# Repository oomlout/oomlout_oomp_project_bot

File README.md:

# oomlout_oomp_documentation_bot_v2

## actions

* action_setup.py -- sets up data and structure
* action_generate_kicad_from_eagle.py -- take all .brd eagle files, open in kicad and save as kicad_pcb and a kicad_sch file
* action_generate_kicad_outputs.py -- (not used anymore) generate the outputs using robo mouse, takes in a kicad_pcb and kicad_sch file
* action_generate_kibot_outputs.py -- all directories with kicad_pcb files get the kibot template from templates/kibot_template.yaml copied to them and kibot is run if the report.txt doesn't exist
* action_generate_image_resolutions.py -- generate resolutions of images
* action_generate_readmes -- generate all the readmes
* action_cleanup_project.py -- cleans up unwanted files from a project directory
* action_harvest_parts.py -- take the working_bom.csv and add parts_verbose to yaml file
* action_match_parts.py -- go trhough each part and match parts_verbose aprts with parts_oomp
* action_find_part.py -- go through all projects and compile a list of all the entries with  search term
* action_rescue_old_kicad_schematic.py -- go through and find all directories that have a kicad_pcb and a .sch file and no schematics generated. Open in kicad 5 and save.

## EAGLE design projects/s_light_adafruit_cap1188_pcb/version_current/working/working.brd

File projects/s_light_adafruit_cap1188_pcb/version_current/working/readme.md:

# Adafruit-CAP1188-PCB by s-light  
This is a harvested standardized copy of a project from github.  
The original project can be found at:  
https://github.com/s-light/Adafruit-CAP1188-PCB  
Please consult that link for additional, details, files, and license information.  
Note: It was auto harvested and if the original repo had more than one board file or anything out of the ordinary the files here are likely not representative.

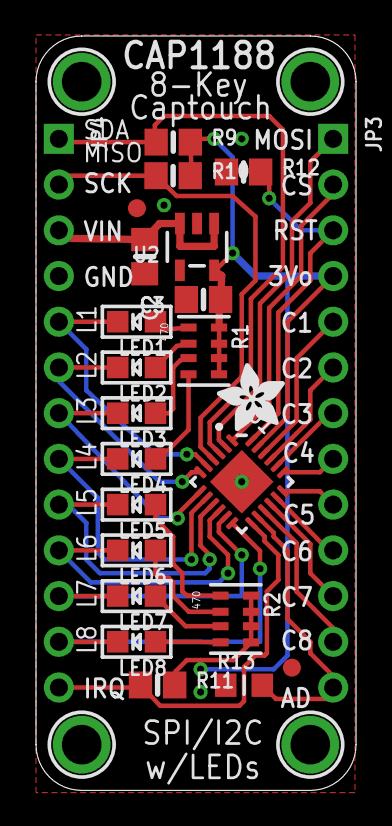
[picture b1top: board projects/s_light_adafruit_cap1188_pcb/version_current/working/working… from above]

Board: 2 copper layers, 17.8 x 41.9 mm, 29 parts (1 on the bottom side), 34 nets.

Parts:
C2, C3: 10uF; 0805-NO
FID1, FID2: FIDUCIAL""; FIDUCIAL_1MM
JP3, JP4: 1X13_ROUND_70
LED1, LED2, LED3, LED4, LED5, LED6, LED7, LED8: CHIPLED_0805
R1, R2: 470; RESPACK_4X0603
R9, R10, R11, R12: 10K; 0805-NO
R13: 150K; _0805MP
U1: QFN24_4MM_SMSC
U2: MIC5225-3; SOT23-5
U$7, U$8, U$9, U$10: MOUNTINGHOLE2.0; MOUNTINGHOLE_2.0_PLATED
U$13: ADAFRUIT_3.5MM
U$14: ADAFRUIT_9MM

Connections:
3.3V: C3.1, JP3.4, R1.5, R1.6, R1.7, R1.8, R2.5, R2.6, R2.7, R2.8, R9.2, R10.2, R11.2, U1.23, U2.5
ADDR: JP3.13, R13.2, U1.14
CS: JP3.2, U1.1
CS1: JP3.5, U1.22
CS2: JP3.6, U1.21
CS3: JP3.7, U1.20
CS4: JP3.8, U1.19
CS5: JP3.9, U1.18
CS6: JP3.10, U1.17
CS7: JP3.11, U1.16
CS8: JP3.12, U1.15
GND: C2.2, C3.2, JP4.4, R12.1, R13.1, U1.THERM, U2.2
IRQ: JP4.13, R11.1, U1.13
LED1: JP4.5, LED1.C, U1.5
LED2: JP4.6, LED2.C, U1.6
LED3: JP4.7, LED3.C, U1.7
LED4: JP4.8, LED4.C, U1.8
LED5: JP4.9, LED5.C, U1.9
LED6: JP4.10, LED6.C, U1.10
LED7: JP4.11, LED7.C, U1.11
LED8: JP4.12, LED8.C, U1.12
unnamed: LED1.A, R1.1
unnamed: LED2.A, R1.2
unnamed: LED3.A, R1.3
unnamed: LED4.A, R1.4
unnamed: LED5.A, R2.1
unnamed: LED6.A, R2.2
unnamed: LED7.A, R2.3
unnamed: LED8.A, R2.4
RESET: JP3.3, R12.2, U1.24
SCK: JP4.2, R10.1, U1.4
SDA/MISO: JP4.1, R9.1, U1.3
VIN: C2.1, JP4.3, U2.1, U2.3
WAKE/MOSI: JP3.1, U1.2

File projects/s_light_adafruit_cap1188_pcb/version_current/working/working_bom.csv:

"Id";"Designator";"Footprint";"Quantity";"Designation";"Supplier and ref";
1;"JP3,JP4";"1X13_ROUND_70";2;"";;;
2;"U2";"SOT23-5";1;"MIC5225-3";;;
3;"LED8,LED2,LED6,LED4,LED7,LED5,LED3,LED1";"CHIPLED_0805";8;"";;;
4;"R9,R12,R11,R10";"0805-NO";4;"10K";;;
5;"U1";"QFN24_4MM_SMSC";1;"";;;
6;"R2,R1";"RESPACK_4X0603";2;"470";;;
7;"U$9,U$7,U$8,U$10";"MOUNTINGHOLE_2.0_PLATED";4;"MOUNTINGHOLE2.0";;;
8;"U$13";"ADAFRUIT_3.5MM";1;"";;;
9;"FID2,FID1";"FIDUCIAL_1MM";2;"FIDUCIAL""";;;
10;"C2,C3";"0805-NO";2;"10uF";;;
11;"R13";"_0805MP";1;"150K";;;
12;"U$14";"ADAFRUIT_9MM";1;"";;;

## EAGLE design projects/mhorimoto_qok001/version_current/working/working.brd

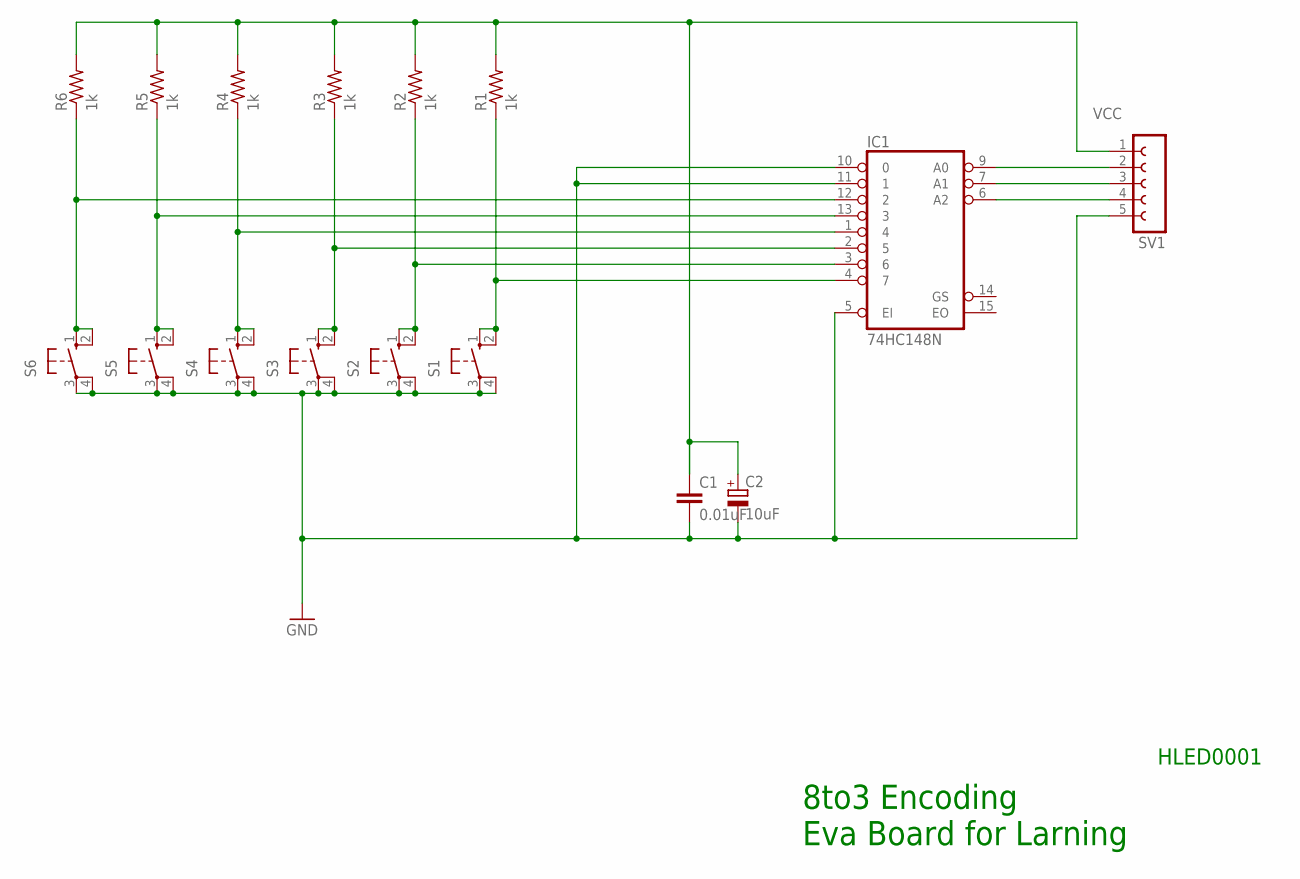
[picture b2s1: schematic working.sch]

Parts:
C1: 0.01uF; C025-025X050
C2: 10uF; E2,5-6E
IC1: 74HC148N; DIL16
R1, R2, R3, R4, R5, R6: 1k; 0207/7
S1, S2, S3, S4, S5, S6: 10-XX; B3F-10XX
SV1: FE05-1

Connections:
GND: C1.2, C2.-, IC1.5 (EI), IC1.8 (GND), IC1.10 (0), IC1.11 (1), S1.3, S1.4 (P1), S2.3, S2.4 (P1), S3.3, S3.4 (P1), S4.3, S4.4 (P1), S5.3, S5.4 (P1), S6.3, S6.4 (P1), SV1.5
unnamed: IC1.4 (7), R1.1, S1.1 (S), S1.2 (S1)
unnamed: IC1.3 (6), R2.1, S2.1 (S), S2.2 (S1)
unnamed: IC1.2 (5), R3.1, S3.1 (S), S3.2 (S1)
unnamed: IC1.1 (4), R4.1, S4.1 (S), S4.2 (S1)
unnamed: IC1.13 (3), R5.1, S5.1 (S), S5.2 (S1)
unnamed: IC1.12 (2), R6.1, S6.1 (S), S6.2 (S1)
unnamed: IC1.9 (A0), SV1.2
unnamed: IC1.7 (A1), SV1.3
unnamed: IC1.6 (A2), SV1.4
VCC: C1.1, C2.+, IC1.16 (VCC), R1.2, R2.2, R3.2, R4.2, R5.2, R6.2, SV1.1

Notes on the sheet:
HLED0001
8to3 Encoding Eva Board for Larning

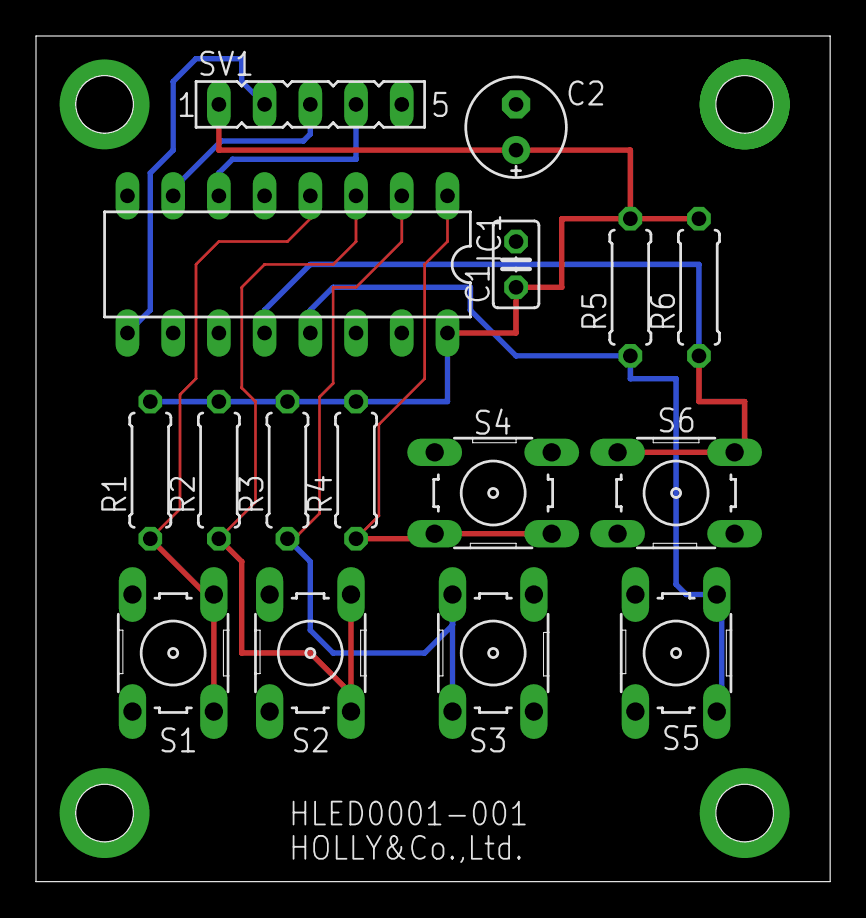
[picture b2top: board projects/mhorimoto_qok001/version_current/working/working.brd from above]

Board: 2 copper layers, 44.1 x 47.0 mm, 16 parts (0 on the bottom side), 11 nets.

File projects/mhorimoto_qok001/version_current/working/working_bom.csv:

"Id";"Designator";"Footprint";"Quantity";"Designation";"Supplier and ref";
1;"S3,S5,S2,S6,S1,S4";"B3F-10XX";6;"";;;
2;"R2,R6,R4,R5,R3,R1";"0207_7";6;"1k";;;
3;"@HOLE0,@HOLE1,@HOLE3,@HOLE2";"";4;"";;;
4;"C1";"C025-025X050";1;"0.01uF";;;
5;"SV1";"FE05-1";1;"";;;
6;"C2";"E2,5-6E";1;"10uF";;;
7;"IC1";"DIL16";1;"74HC148N";;;

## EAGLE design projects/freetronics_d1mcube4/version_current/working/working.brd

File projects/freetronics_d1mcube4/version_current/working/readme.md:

# OOMP Project  
## D1MCUBE4  by freetronics  
  
oomp key: oomp_projects_flat_freetronics_d1mcube4  
(snippet of original readme)  
  
4x4x4 RGB LED Cube for the WeMos D1 Mini  
=========================================  
  
Copyright 2017 Freetronics Pty Ltd  www.freetronics.com.au    
  
4x4x4 RGB LED cube that can be controlled by a [WeMos D1 Mini][1], a  
microcontroller board based on the ESP8266 module.  
  
Features:  
  
 * 64 x 8mm addressable RGB LEDs (APA106)  
 * 2.1mm DC jack and solder terminal connections for power input.  
  
More information is available at:  
  
  http://www.freetronics.com.au/d1mcube4  

INSTALLATION  
------------  
The design is saved as an EAGLE project. EAGLE PCB design software is  
available from www.cadsoftusa.com free for non-commercial use. To use  
this project download it and place the directory containing these files  
into the "eagle" directory on your computer, then navigate to the  
project.  

DISTRIBUTION  
------------  
The specific terms of distribution of this project are governed by the  
license referenced below.  

LICENSE  
-------  
Licensed under the TAPR Open Hardware License (www.tapr.org/OHL).  
The "license" folder within this repository also contains a copy of  
this license in plain text format.  

[1]: http://www.wemos.cc/wiki/doku.php?id=en:d1_mini  

  full source readme at [readme_src.md](readme_src.md)  
  
source repo at: [https://github.com/freetronics/D1MCUBE4](https://github.com/freetronics/D1MCUBE4)  
## Board  

## Schematic  

[schematic pdf](working_schematic.pdf)  
## Images

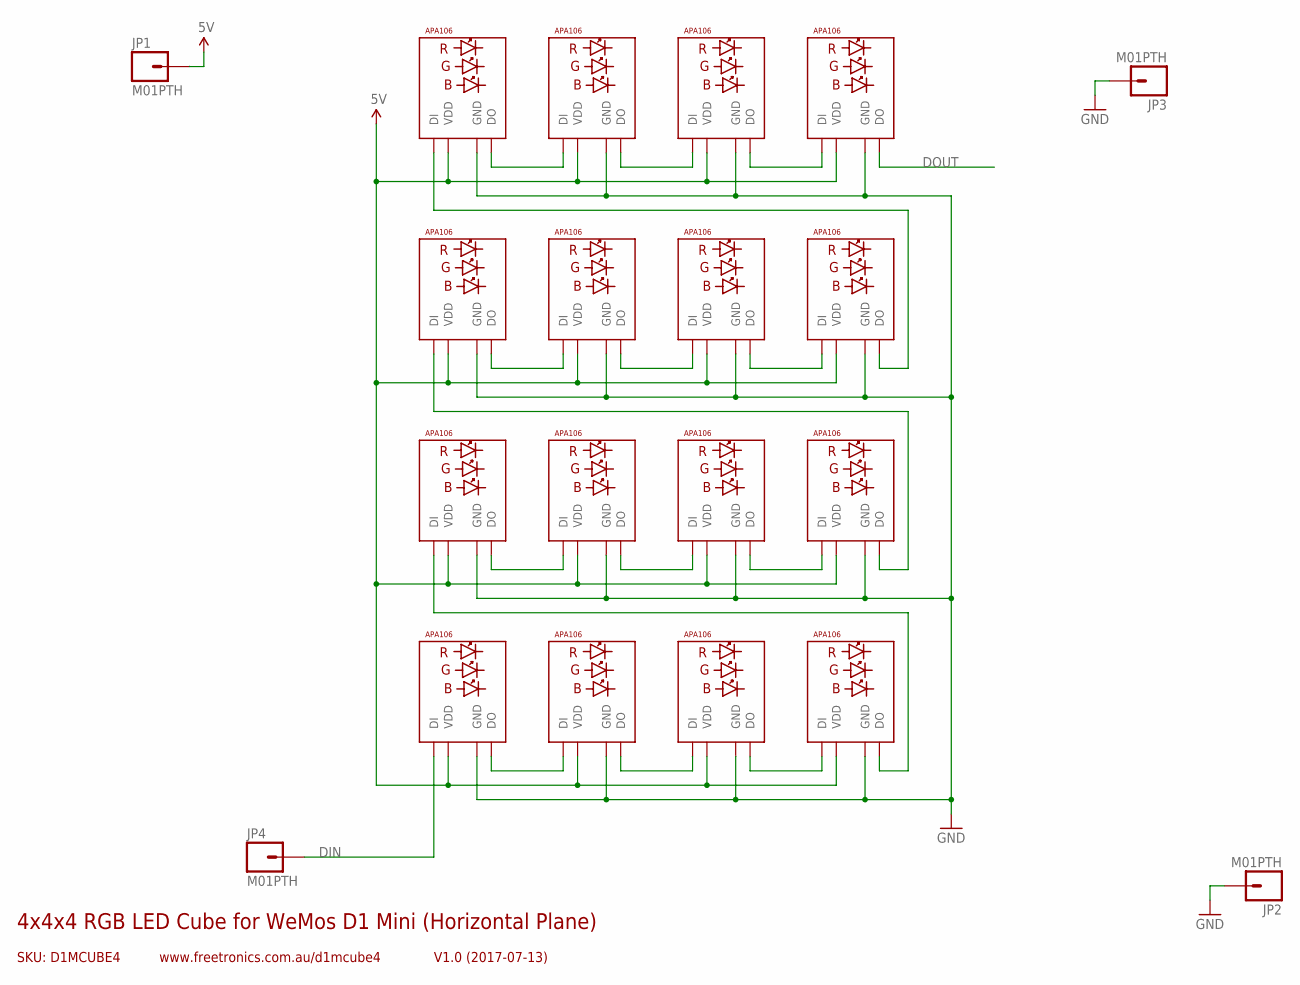
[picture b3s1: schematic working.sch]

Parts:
JP1, JP2, JP3, JP4: M01PTH; 1X01
LED1, LED2, LED3, LED4, LED5, LED6, LED7, LED8, LED9, LED10, LED11, LED12, LED13, LED14, LED15, LED16: APA106F8; LED8MMRGB

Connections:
5V: JP1.1, LED1.3 (VDD), LED2.3 (VDD), LED3.3 (VDD), LED4.3 (VDD), LED5.3 (VDD), LED6.3 (VDD), LED7.3 (VDD), LED8.3 (VDD), LED9.3 (VDD), LED10.3 (VDD), LED11.3 (VDD), LED12.3 (VDD), LED13.3 (VDD), LED14.3 (VDD), LED15.3 (VDD), LED16.3 (VDD)
DIN: JP4.1, LED1.4 (DI)
DOUT: LED16.1 (DO)
GND: JP2.1, JP3.1, LED1.2 (GND), LED2.2 (GND), LED3.2 (GND), LED4.2 (GND), LED5.2 (GND), LED6.2 (GND), LED7.2 (GND), LED8.2 (GND), LED9.2 (GND), LED10.2 (GND), LED11.2 (GND), LED12.2 (GND), LED13.2 (GND), LED14.2 (GND), LED15.2 (GND), LED16.2 (GND)
unnamed: LED1.1 (DO), LED2.4 (DI)
unnamed: LED2.1 (DO), LED3.4 (DI)
unnamed: LED3.1 (DO), LED4.4 (DI)
unnamed: LED13.1 (DO), LED14.4 (DI)
unnamed: LED14.1 (DO), LED15.4 (DI)
unnamed: LED15.1 (DO), LED16.4 (DI)
unnamed: LED9.1 (DO), LED10.4 (DI)
unnamed: LED10.1 (DO), LED11.4 (DI)
unnamed: LED11.1 (DO), LED12.4 (DI)
unnamed: LED5.1 (DO), LED6.4 (DI)
unnamed: LED6.1 (DO), LED7.4 (DI)
unnamed: LED7.1 (DO), LED8.4 (DI)
unnamed: LED12.1 (DO), LED13.4 (DI)
unnamed: LED4.1 (DO), LED5.4 (DI)
unnamed: LED8.1 (DO), LED9.4 (DI)

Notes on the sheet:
SKU: D1MCUBE4
4x4x4 RGB LED Cube for WeMos D1 Mini (Horizontal Plane)
V1.0 (2017-07-13)
www.freetronics.com.au/d1mcube4

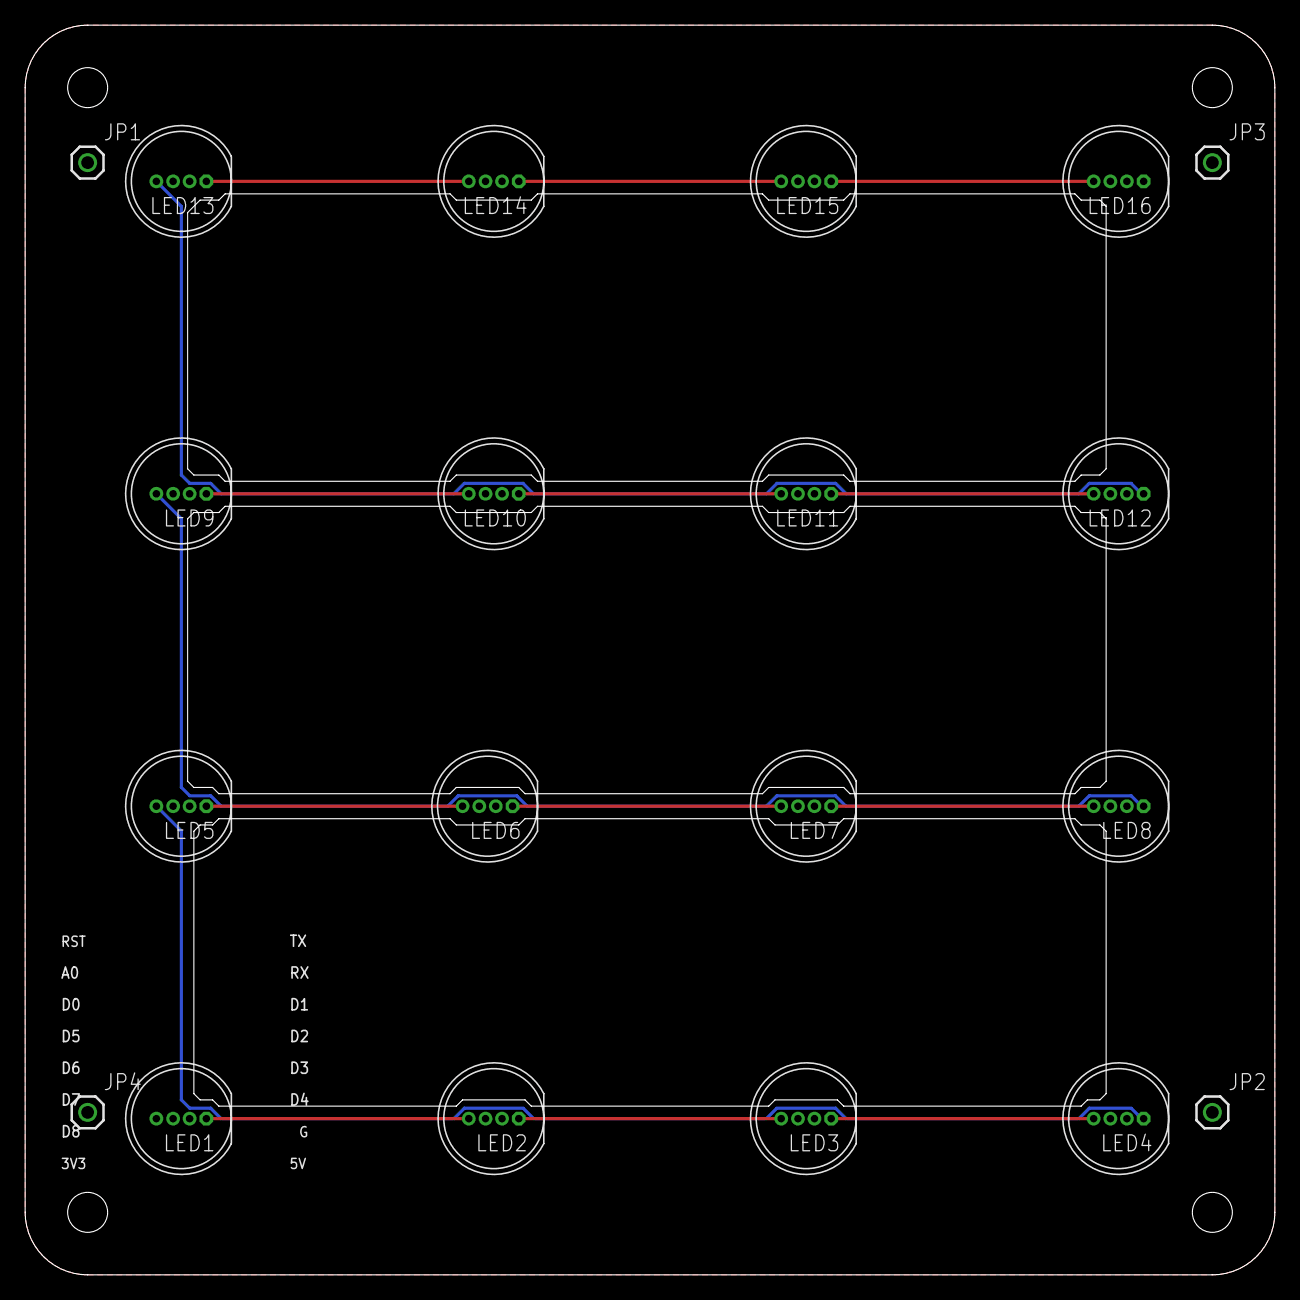
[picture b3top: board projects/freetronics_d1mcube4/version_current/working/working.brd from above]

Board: 2 copper layers, 100.0 x 100.0 mm, 20 parts (0 on the bottom side), 18 nets.

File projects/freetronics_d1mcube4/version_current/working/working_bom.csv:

"Id";"Designator";"Footprint";"Quantity";"Designation";"Supplier and ref";
1;"@HOLE3,@HOLE0,@HOLE2,@HOLE1";"";4;"";;;
2;"LED13,LED10,LED9,LED6,LED8,LED12,LED3,LED7,LED5,LED16,LED4,LED15,LED11,LED1,LED14,LED2";"LED8MMRGB";16;"APA106F8";;;
3;"JP1,JP4,JP3,JP2";"1X01";4;"M01PTH";;;

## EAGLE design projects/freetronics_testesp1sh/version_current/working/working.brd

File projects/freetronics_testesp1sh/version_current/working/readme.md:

# TESTESP1SH by freetronics  
This is a harvested standardized copy of a project from github.  
The original project can be found at:  
https://github.com/freetronics/TESTESP1SH  
Please consult that link for additional, details, files, and license information.  
Note: It was auto harvested and if the original repo had more than one board file or anything out of the ordinary the files here are likely not representative.

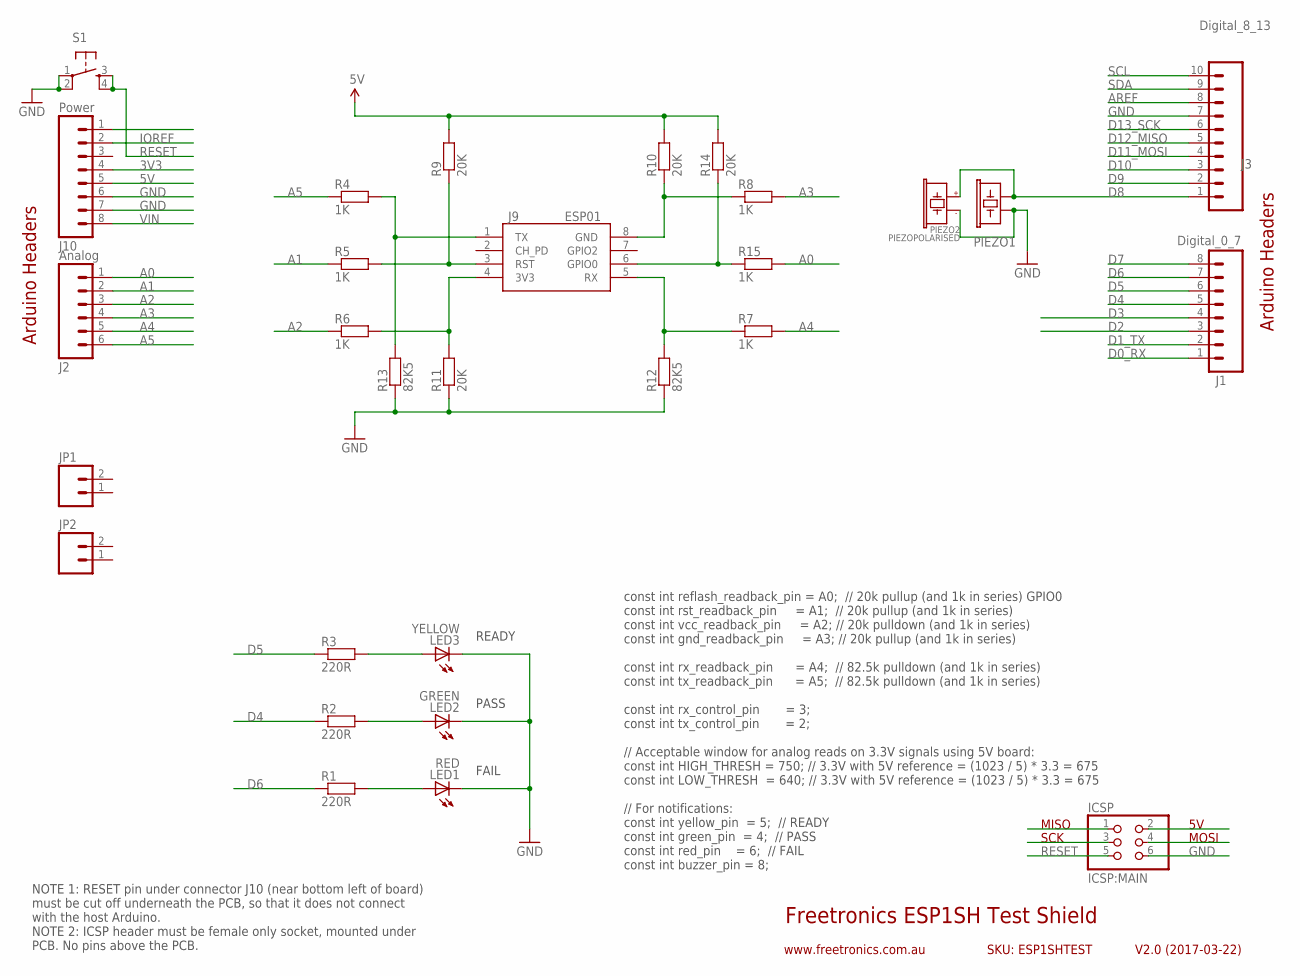
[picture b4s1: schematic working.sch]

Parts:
ICSP: ICSP:MAIN; 2X03
J1: Digital_0_7; 1X08
J2: Analog; 1X06
J3: Digital_8_13; 1X10
J9: ESP01
J10: Power; 1X08
JP1, JP2: M02PTH; 1X02
LED1: RED; LED-0603
LED2: GREEN; LED-0603
LED3: YELLOW; LED-0603
PIEZO1: BUZZERSMD12X12; BUZZER-12X12-SMT
PIEZO2: PIEZOPOLARISED; PIEZO12MMWIDEPOLARISED
R1, R2, R3: 220R; 0603
R4, R5, R6, R7, R8, R15: 1K; 0603
R9, R10, R11, R14: 20K; 0603
R12, R13: 82K5; 0603
S1: TAC_SWITCHPTH; TACTILE-PTH

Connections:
3V3: J10.4
5V: J10.5, R9.2, R10.2, R14.2
A0: J2.1, R15.2
A1: J2.2, R5.1
A2: J2.3, R6.1
A3: J2.4, R8.2
A4: J2.5, R7.2
A5: J2.6, R4.1
AREF: J3.8
D0_RX: J1.1
D1_TX: J1.2
D2: J1.3
D3: J1.4
D4: J1.5, R2.1
D5: J1.6, R3.1
D6: J1.7, R1.1
D7: J1.8
D8: J3.1, PIEZO1.1, PIEZO2.1 (+)
D9: J3.2
D10: J3.3
D11_MOSI: J3.4
D12_MISO: J3.5
D13_SCK: J3.6
GND: ICSP.6, J3.7, J10.6, J10.7, LED1.C, LED2.C, LED3.C, PIEZO1.2, PIEZO2.2 (-), R11.1, R12.1, R13.1, S1.1, S1.2
IOREF: J10.2
unnamed: LED3.A, R3.2
unnamed: LED2.A, R2.2
unnamed: LED1.A, R1.2
unnamed: J9.3 (RST), R5.2, R9.1
unnamed: J9.8 (GND), R8.1, R10.1
unnamed: J9.4 (3V3), R6.2, R11.2
unnamed: J9.5 (RX), R7.1, R12.2
unnamed: J9.1 (TX), R4.2, R13.2
unnamed: J9.6 (GPIO0), R14.1, R15.1
RESET: ICSP.5, S1.3, S1.4
SCL: J3.10
SDA: J3.9
VIN: J10.8

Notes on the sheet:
Freetronics ESP1SH Test Shield
V2.0 (2017-03-22)
www.freetronics.com.au
SKU: ESP1SHTEST
Arduino Headers
MISO
SCK
MOSI
READY
PASS
FAIL
NOTE 1: RESET pin under connector J10 (near bottom left of board) must be cut off underneath the PCB, so that it does not connect with the host Arduino. NOTE 2: ICSP header must be female only socket, mounted under PCB. No pins above the PCB.
const int reflash_readback_pin = A0; // 20k pullup (and 1k in series) GPIO0 const int rst_readback_pin = A1; // 20k pullup (and 1k in series) const int vcc_readback_pin = A2; // 20k pulldown (and 1k in series) const int gnd_readback_pin = A3; // 20k pullup (and 1k in series) const int rx_readback_p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

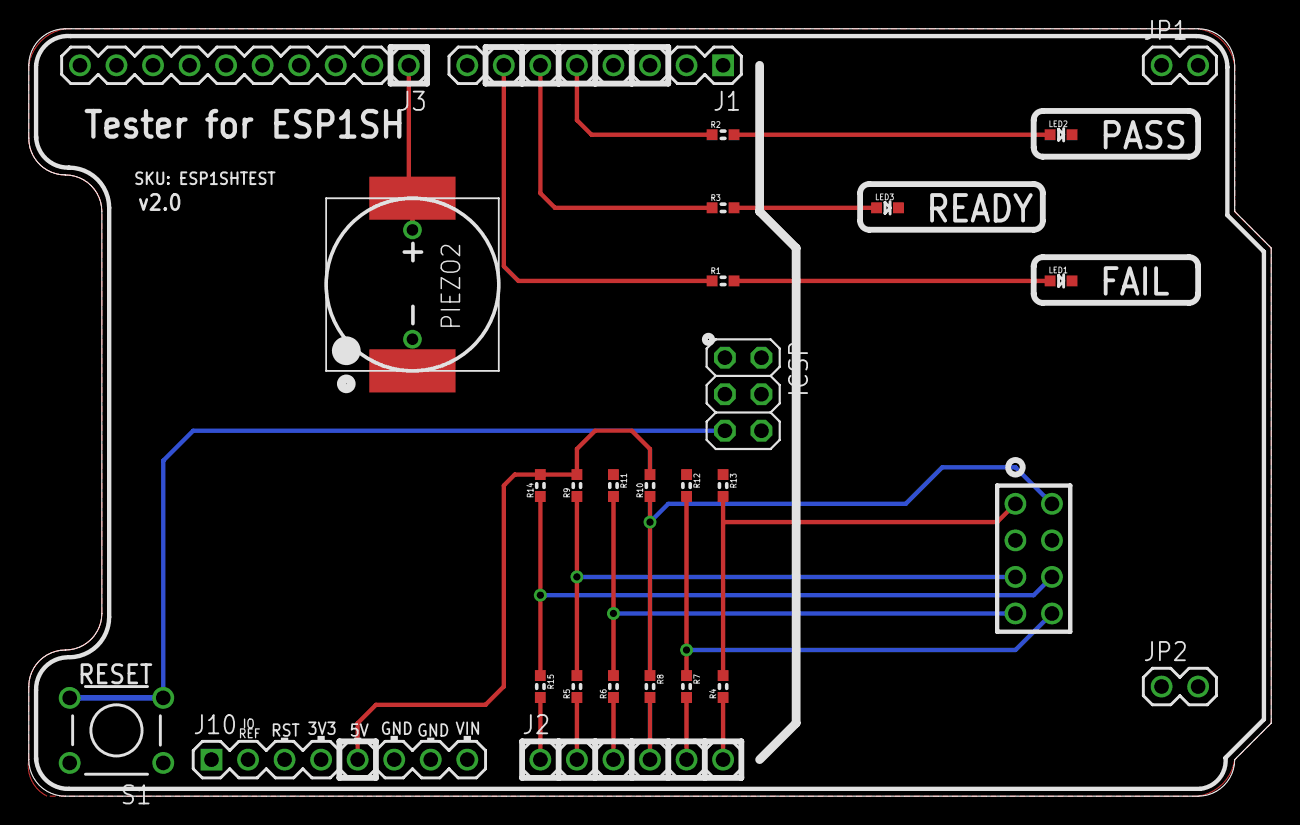
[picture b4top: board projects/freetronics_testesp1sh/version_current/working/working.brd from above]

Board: 2 copper layers, 86.4 x 53.3 mm, 29 parts (0 on the bottom side), 22 nets.

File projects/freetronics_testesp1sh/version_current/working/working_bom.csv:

"Id";"Designator";"Footprint";"Quantity";"Designation";"Supplier and ref";
1;"J1";"1X08";1;"Digital_0_7";;;
2;"R8,R4,R7,R6,R5,R15";"0603";6;"1K";;;
3;"R11,R9,R10,R14";"0603";4;"20K";;;
4;"LED1";"LED-0603";1;"RED";;;
5;"R2,R3,R1";"0603";3;"220R";;;
6;"JP1,JP2";"1X02";2;"";;;
7;"ICSP0";"2X03";1;"ICSP:MAIN";;;
8;"LED3";"LED-0603";1;"YELLOW";;;
9;"R12,R13";"0603";2;"82K5";;;
10;"PIEZO2";"PIEZO12MMWIDEPOLARISED";1;"PIEZOPOLARISED";;;
11;"LED2";"LED-0603";1;"GREEN";;;
12;"S1";"TACTILE-PTH";1;"";;;
13;"J2";"1X06";1;"Analog";;;
14;"J9";"ESP01";1;"ESP01";;;
15;"J10";"1X08";1;"Power";;;
16;"J3";"1X10";1;"Digital_8_13";;;
17;"PIEZO1";"BUZZER-12X12-SMT";1;"BUZZERSMD12X12";;;

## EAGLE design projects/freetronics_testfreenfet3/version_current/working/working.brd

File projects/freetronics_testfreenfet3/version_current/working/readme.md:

# TESTFREENFET3 by freetronics  
This is a harvested standardized copy of a project from github.  
The original project can be found at:  
https://github.com/freetronics/TESTFREENFET3  
Please consult that link for additional, details, files, and license information.  
Note: It was auto harvested and if the original repo had more than one board file or anything out of the ordinary the files here are likely not representative.

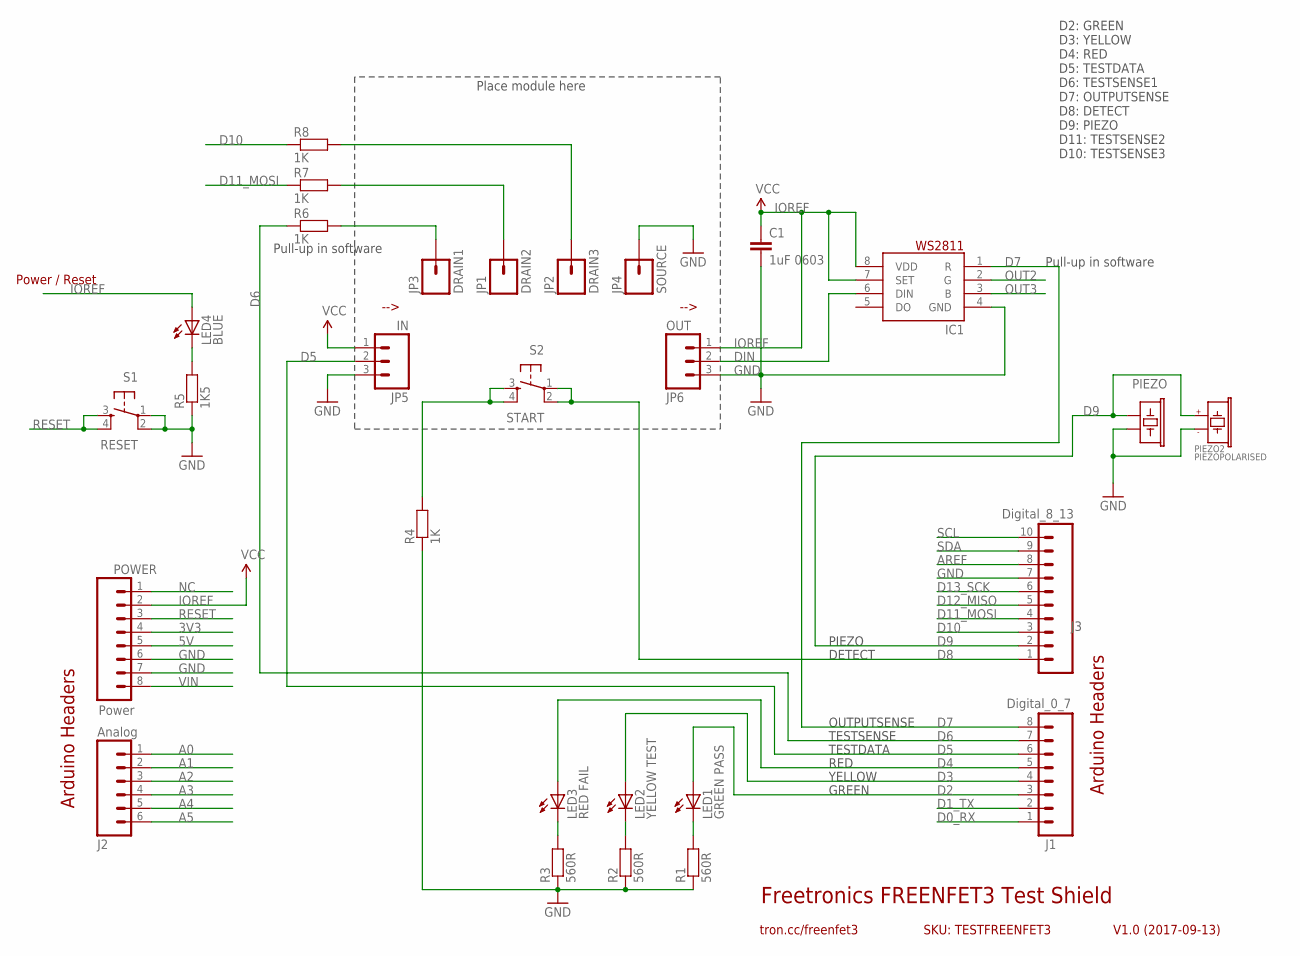
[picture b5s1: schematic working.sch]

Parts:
C1: 1uF 0603; 0603
IC1: WS2811-SOP8; SO08-SKINNYPADS
J1: Digital_0_7; 1X08
J2: Analog; 1X06
J3: Digital_8_13; 1X10
JP1: DRAIN2; 1X01_2_1_MM
JP2: DRAIN3; 1X01_2_1_MM
JP3: DRAIN1; 1X01_2_1_MM
JP4: SOURCE; 1X01_2_1_MM
JP5: IN; 1X03
JP6: OUT; 1X03
LED1: GREEN PASS; LED-0603
LED2: YELLOW TEST; LED-0603
LED3: RED FAIL; LED-0603
LED4: BLUE; LED-0603
PIEZO: BUZZERSMD12X12; BUZZER-12X12-SMT
PIEZO2: PIEZOPOLARISED; PIEZO12MMWIDEPOLARISED
POWER: Power; 1X08
R1, R2, R3: 560R; 0603
R4, R6, R7, R8: 1K; 0603
R5: 1K5; 0603
S1: RESET; TACTILE-PTH
S2: START; TACTILE-PTH

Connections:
3V3: POWER.4
5V: POWER.5
A0: J2.1
A1: J2.2
A2: J2.3
A3: J2.4
A4: J2.5
A5: J2.6
AREF: J3.8
D0_RX: J1.1
D1_TX: J1.2
D2: J1.3, LED1.A
D3: J1.4, LED2.A
D4: J1.5, LED3.A
D5: J1.6, JP5.2
D6: J1.7, R6.1
D7: IC1.1 (R), J1.8
D8: J3.1, S2.1, S2.2
D9: J3.2, PIEZO.2, PIEZO2.1 (+)
D10: J3.3, R8.1
D11_MOSI: J3.4, R7.1
D12_MISO: J3.5
D13_SCK: J3.6
DIN: IC1.6 (DIN), JP6.2
GND: C1.2, IC1.4 (GND), J3.7, JP4.1, JP5.3, JP6.3, PIEZO.1, PIEZO2.2 (-), POWER.6, POWER.7, R1.1, R2.1, R3.1, R4.1, R5.1, S1.1, S1.2
IOREF: C1.1, IC1.7 (SET), IC1.8 (VDD), JP5.1, JP6.1, LED4.A, POWER.2
unnamed: LED1.C, R1.2
unnamed: LED2.C, R2.2
unnamed: LED3.C, R3.2
unnamed: LED4.C, R5.2
unnamed: JP3.1, R6.2
unnamed: JP1.1, R7.2
unnamed: R4.2, S2.3, S2.4
unnamed: JP2.1, R8.2
NC: POWER.1
OUT2: IC1.2 (G)
OUT3: IC1.3 (B)
RESET: POWER.3, S1.3, S1.4
SCL: J3.10
SDA: J3.9
VIN: POWER.8

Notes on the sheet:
Freetronics FREENFET3 Test Shield
V1.0 (2017-09-13)
tron.cc/freenfet3
SKU: TESTFREENFET3
Arduino Headers
Power / Reset
-->
Pull-up in software
Place module here
D2: GREEN D3: YELLOW D4: RED D5: TESTDATA D6: TESTSENSE1 D7: OUTPUTSENSE D8: DETECT D9: PIEZO D11: TESTSENSE2 D10: TESTSENSE3
TESTDATA
GREEN
YELLOW
RED
TESTSENSE
OUTPUTSENSE
DETECT
PIEZO

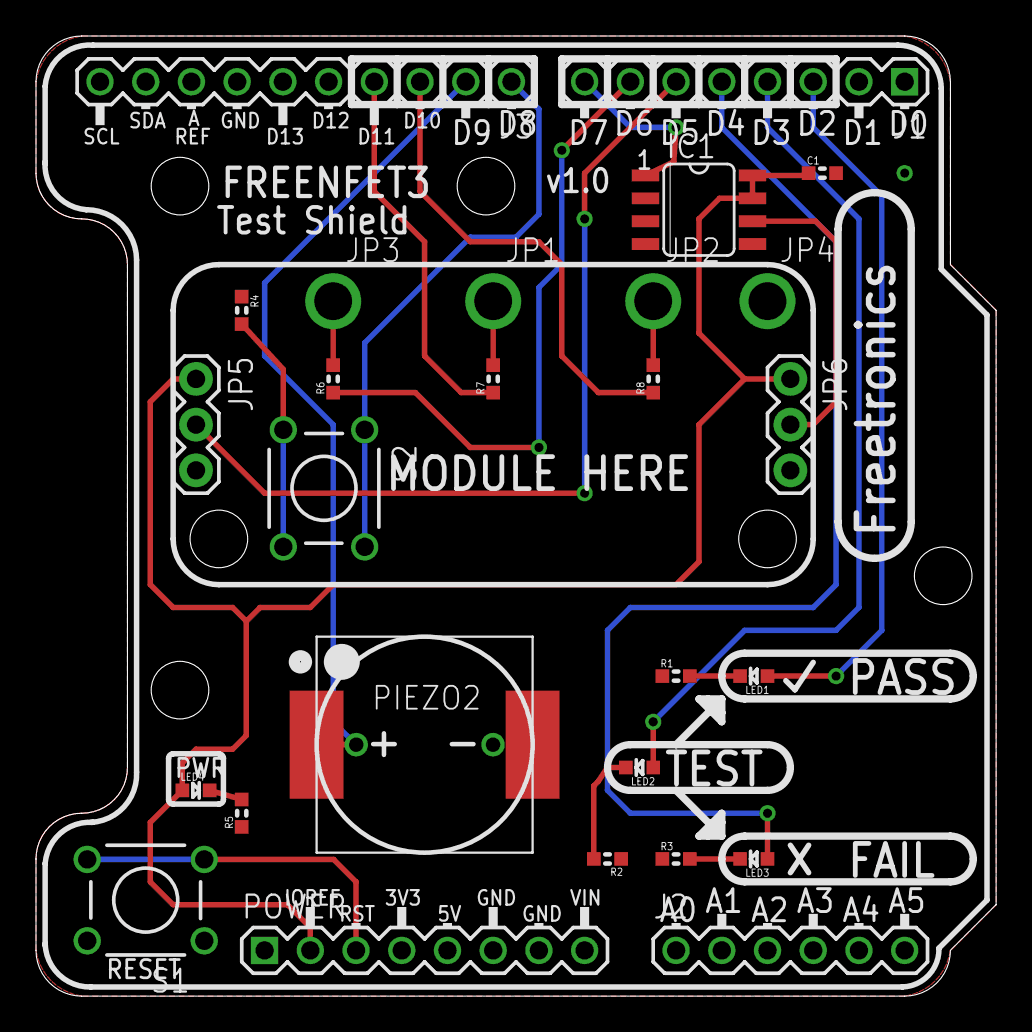
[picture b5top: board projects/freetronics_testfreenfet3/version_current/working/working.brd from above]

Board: 2 copper layers, 53.3 x 53.3 mm, 28 parts (0 on the bottom side), 22 nets.

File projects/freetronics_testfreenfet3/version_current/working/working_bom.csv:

"Id";"Designator";"Footprint";"Quantity";"Designation";"Supplier and ref";
1;"PIEZO2";"PIEZO12MMWIDEPOLARISED";1;"PIEZOPOLARISED";;;
2;"R7,R6,R8,R4";"0603";4;"1K";;;
3;"JP4";"1X01_2_1_MM";1;"SOURCE";;;
4;"@HOLE4,@HOLE0,@HOLE1,@HOLE5,@HOLE3,@HOLE2";"";6;"";;;
5;"LED4";"LED-0603";1;"BLUE";;;
6;"J3";"1X10";1;"Digital_8_13";;;
7;"J2";"1X06";1;"Analog";;;
8;"JP3";"1X01_2_1_MM";1;"DRAIN1";;;
9;"JP1";"1X01_2_1_MM";1;"DRAIN2";;;
10;"R5";"0603";1;"1K5";;;
11;"R3,R1,R2";"0603";3;"560R";;;
12;"J1";"1X08";1;"Digital_0_7";;;
13;"LED3";"LED-0603";1;"RED FAIL";;;
14;"JP2";"1X01_2_1_MM";1;"DRAIN3";;;
15;"PIEZO0";"BUZZER-12X12-SMT";1;"BUZZERSMD12X12";;;
16;"JP5";"1X03";1;"IN";;;
17;"S1";"TACTILE-PTH";1;"RESET";;;
18;"POWER0";"1X08";1;"Power";;;
19;"LED2";"LED-0603";1;"YELLOW TEST";;;
20;"IC1";"SO08-SKINNYPADS";1;"WS2811-SOP8";;;
21;"JP6";"1X03";1;"OUT";;;
22;"LED1";"LED-0603";1;"GREEN PASS";;;
23;"C1";"0603";1;"1uF 0603";;;
24;"S2";"TACTILE-PTH";1;"START";;;

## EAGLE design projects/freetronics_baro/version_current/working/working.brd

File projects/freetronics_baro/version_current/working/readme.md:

# BARO by freetronics  
This is a harvested standardized copy of a project from github.  
The original project can be found at:  
https://github.com/freetronics/BARO  
Please consult that link for additional, details, files, and license information.  
Note: It was auto harvested and if the original repo had more than one board file or anything out of the ordinary the files here are likely not representative.

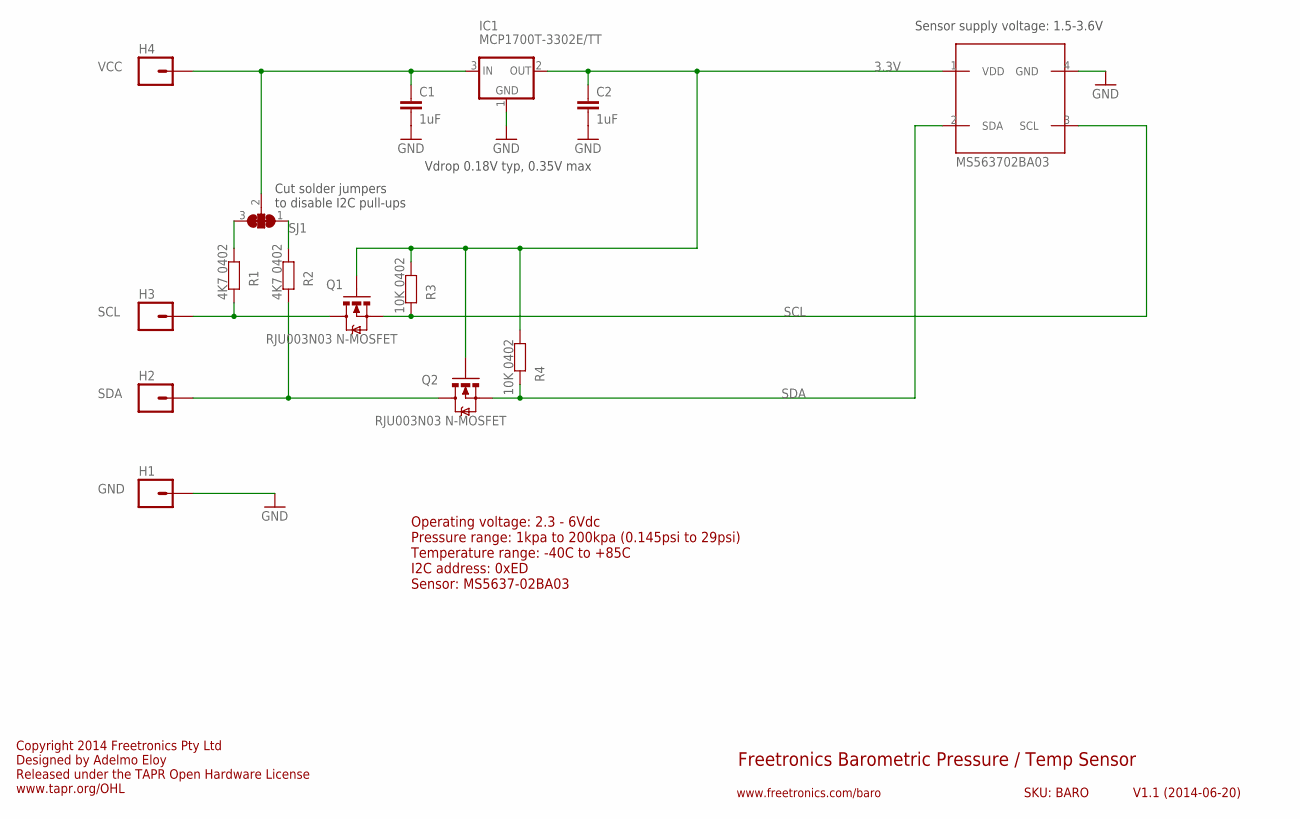
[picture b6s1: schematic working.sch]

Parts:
C1, C2: 1uF; 0603
H1: GND; 1X01
H2: SDA; 1X01
H3: SCL; 1X01
H4: VCC; 1X01
IC1: MCP1700T-3302E/TT; SOT23-3
IC2: MS563702BA03; MS5637
Q1, Q2: RJU003N03 N-MOSFET; SOT32-3
R1, R2: 4K7 0402; 0402
R3, R4: 10K 0402; 0402
SJ1: SJ2W; SJ_2

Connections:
3.3V: C2.1, IC1.2 (OUT), IC2.1 (VDD), Q1.1 (G), Q2.1 (G), R3.2, R4.2
GND: C1.2, C2.2, H1.1, IC1.1 (GND), IC2.4 (GND)
unnamed: IC2.3 (SCL), Q1.2 (S), R3.1
unnamed: C1.1, H4.1, IC1.3 (IN), SJ1.2
unnamed: IC2.2 (SDA), Q2.2 (S), R4.1
unnamed: R1.2, SJ1.3
unnamed: R2.2, SJ1.1
SCL: H3.1, Q1.3 (D), R1.1
SDA: H2.1, Q2.3 (D), R2.1

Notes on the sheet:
Freetronics Barometric Pressure / Temp Sensor
V1.1 (2014-06-20)
www.freetronics.com/baro
SKU: BARO
Sensor supply voltage: 1.5-3.6V
Cut solder jumpers to disable I2C pull-ups
Vdrop 0.18V typ, 0.35V max
Copyright 2014 Freetronics Pty Ltd Designed by Adelmo Eloy Released under the TAPR Open Hardware License www.tapr.org/OHL
Operating voltage: 2.3 - 6Vdc Pressure range: 1kpa to 200kpa (0.145psi to 29psi) Temperature range: -40C to +85C I2C address: 0xED Sensor: MS5637-02BA03

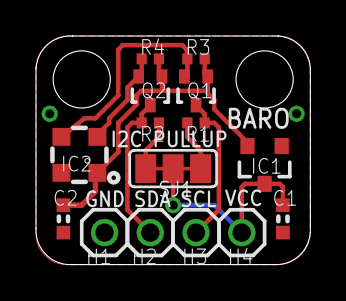
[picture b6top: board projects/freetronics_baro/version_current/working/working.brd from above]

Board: 2 copper layers, 15.2 x 12.7 mm, 15 parts (0 on the bottom side), 9 nets.

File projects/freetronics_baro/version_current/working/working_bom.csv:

"Id";"Designator";"Footprint";"Quantity";"Designation";"Supplier and ref";
1;"H1";"1X01";1;"GND";;;
2;"@HOLE1,@HOLE0";"";2;"";;;
3;"H4";"1X01";1;"VCC";;;
4;"Q2,Q1";"SOT32-3";2;"RJU003N03 N-MOSFET";;;
5;"R3,R4";"0402";2;"10K 0402";;;
6;"H2";"1X01";1;"SDA";;;
7;"R2,R1";"0402";2;"4K7 0402";;;
8;"IC1";"SOT23-3";1;"MCP1700T-3302E/TT";;;
9;"IC2";"MS5637";1;"MS563702BA03";;;
10;"C1,C2";"0603";2;"1uF";;;
11;"H3";"1X01";1;"SCL";;;
12;"SJ1";"SJ_2";1;"";;;

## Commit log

2023-07-30 a few generations
2023-07-31 some generations
2023-08-01 converted omerk brd to kicad
2023-08-02 a few projects
2023-08-02 some documentation
2023-08-03 more kicad files
2023-08-03 added kibot files for projects
2023-08-03 removed oom_kicad dependancy
2023-08-03 added print statement
2023-08-03 added kicad_sch check to deal with old kicad format issues
2023-08-03 more verbose command line arg.
2023-08-03 even more verbose.
2023-08-03 added an overwrite check
2023-08-03 first gitbot try
2023-08-03 up to date
2023-08-03 added some gitbot
2023-08-03 comitting after 1 generations
2023-08-03 comitting after 2 generations
2023-08-03 comitting after 30 generations
2023-08-03 comitting after 60 generations
2023-08-03 comitting after 90 generations
2023-08-03 comitting after 120 generations
2023-08-03 comitting after 150 generations
2023-08-03 comitting after 180 generations
2023-08-03 comitting after 210 generations
2023-08-03 comitting after 240 generations
2023-08-03 comitting after 270 generations
2023-08-03 comitting after 50 generations
2023-08-03 comitting after 100 generations
2023-08-03 comitting after 200 generations
2023-08-04 comitting after 250 generations
2023-08-04 comitting after 300 generations
2023-08-04 comitting after 350 generations
2023-08-04 comitting after 400 generations
2023-08-04 comitting after 450 generations
2023-08-04 comitting after 500 generations
2023-08-04 comitting after 550 generations
2023-08-04 comitting after 600 generations
2023-08-04 comitting after 650 generations
2023-08-04 a checkup
2023-08-04 more project translations
2023-08-04 adding some more renders
2023-08-05 comitting after 700 generations
2023-08-06 a few renders
2023-08-06 adding a few more eagle projects as kicad
2023-08-06 some stuff
2023-08-07 adding 775
2023-08-07 quick commit
2023-08-07 updated all projects from src
2023-08-07 a few extra
2023-08-07 a few gens
2023-08-07 oshcamp update
2023-08-07 oshcamp kicad_pcbs
2023-08-07 oshcamp gen
2023-08-07 added oshcamp bom
2023-08-08 bringing up to date.
2023-08-08 added readmes
2023-08-08 added oomp_key to project
2023-08-14 added parts_verbose
2023-08-16 added some converted schematics
2023-08-16 some schematic pdfs
2023-08-16 added a few rescued schematics
2023-08-17 more kicad older version rescues
2023-08-18 added some captures
2023-08-20 almost all rescued kicad schematics
2023-08-20 a bunch of harvesting
2023-08-27 some gens
2023-08-29 resyncing
2023-08-29 comitting after 5000 generations
2023-08-29 comitting after 10000 generations
2023-08-29 comitting after 15000 generations
2023-08-29 image resolutions
2023-08-30 added match md
2023-08-30 fixed projects.yaml location
2023-08-30 fixed link
2023-09-05 complete run

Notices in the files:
projects/freetronics_baro/version_current/working/working.brd:
(c) 2014 Freetronics
projects/freetronics_d1mcube4/version_current/working/working.brd:
(C)2017 Freetronics Pty Ltd
projects/freetronics_testesp1sh/version_current/working/working.brd:
(C) 2017
parts and their libraries:
freetronics-original: Licensing: CC v3.0 Share-Alike You are welcome to use this library for commercial purposes.
microbuilder: This work is placed in the public domain, and may be freely used for commercial and non-commercial work with the following conditions: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
